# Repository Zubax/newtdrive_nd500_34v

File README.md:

# NewtDrive ND500-34V / Zubax Sadulli

Sadulli is an open-hardware reference design of a 500 W integrated propeller drive based on the
[Mitochondrik LV](http://zubax.com/mitochondrik-lv) motor control chip.
It includes a motor and its control electronics in a single compact unit.

The main design goal is to create a compact yet sophisticated motor controller that can be integrated with relatively
small BLDC and PMSM motors (about 40-45 mm in diameter) in a single unit.
Being equipped with a standard mounting hole pattern,
Sadulli can be used as a drop-in replacement for regular standalone motors in various UAV applications.

## Specifications

- Operating voltage range: 4-8S Li-ion LiCoO<sub>2</sub>, 11-34 V
- Maximum continuous power 500 W
- Maximum continuous phase current amplitude 40 A
- [Cyphal](https://telega.zubax.com/)/CAN (formerly UAVCAN) interface compatible with the DS-015 drone standard
- Solderless integration

Sadulli consists of two main parts: a COTS motor and the ESC.
This repository contains the ESC hardware source files only.
There are two design variants of the Sadulli drive.
All of them share the same ESC design.

Variant  | Motor                 | Propeller diameter [inch] | Propeller pitch [inch] | Mass [g]
-------- | --------------------- | ------------------------- | ---------------------- | --------
Alakdan  | Scorpion MII-4010     | 17                        | 6.2                    | 193
Nudo     | N/A                   | N/A                       | N/A                    | 62

Alakdan | Nudo
--|--
 | 

Sadulli is equipped with a single non-redundant Cyphal/CAN interface.
The input power is supplied through a standard XT30 male connector.
The device can deliver 5V to the Cyphal/CAN power delivery network if the respective configuration option is enabled.

Under the hood, Sadulli is a construction of three PCBs (excluding the Mitochondrik).

The main PCB that determines most of Sadulli's properties is the power stage PCB.
The power stage is composed of three [BUK9K6R2-40E](https://www.digikey.com/products/en?keywords=1727-7274-1-ND)
MOSFET arrays.

Parameter                                               | Value
------------------------------------------------------- | -------------------
Drain to Source Voltage (V<sub>ds</sub>)                | 40 V
Current - Continuous Drain (I<sub>d</sub>) @ 25°C       | 40 A
R<sub>ds on</sub> (Max) @ I<sub>d</sub>, V<sub>gs</sub> | 6 mOhm @ 25 A, 10 V
Gate Charge (Q<sub>g</sub>) (Max) @ V<sub>gs</sub>      | 35.4 nC @ 10 V

The resistance of the phase current shunts is 3 mOhm.

The bulk capacitor bank is formed with 6
[68µF aluminum electrolytic capacitors](https://www.digikey.com/product-detail/en/w-rth-elektronik/860020673014/732-8860-3-ND/5727097).

### Telega configuration

The Mitochondrik LV module installed in Sadulli needs to be configured such that it is aware of the parameters of the power stage
(and the motor).
To achieve this, upload the following configuration:

```yaml
# Refer to the Mitochondrik-LV datasheet for the explanation of how the parameter values have been found.
vsi.bridge_resistance:    [0.003, 0.006, 0.003, 0.006, 0.003, 0.003]                            # [ohm]
vsi.phase_current_gain:   [33.333333333333, 33.333333333333, 8.333333333333, 8.333333333333]    # [ampere/volt]
vsi.phase_current_stderr: [0.2, 0.2, 0.1, 0.1]                                                  # [ampere]
vsi.thermistor_v2k:       [223.15, 100.0, 0.0]                                                  # for MCP9700

motor.current_ctl_bwr:  0.04
motor.current_max:      38.0
motor.mechanical_ratio: 7                   # The motor has 14 poles.
motor.inductance_dq:    [29.0e-6, 29.0e-6]
motor.resistance:       0.0508
motor.flux_linkage:     0.002115
motor.current_ramp:     5000.0
motor.voltage_ramp:     20.0
# The thermistor coefficients are valid for:
# R_pull = 1.2 kohms; R_io = 0; V_pull = 3.3 V
# Thermistor models: KTY81/120, KTY81/110, KTY81/121, KTY81/122, KTY81/150, 102PS1J, 102PS1G.
motor.thermistor_v2k: [151.24172662, 36.46076996, 40.65372514]

aux.pull: +1                    # Pull up the thermistor input.

sys.debug: false                # Turn off the in-circuit debug interfaces to enhance EMI immunity.
sys.golden: sys. vsi. motor. aux.pull # Retain these parameter groups across a factory reset.
```

Refer to the Telega Reference Manual for details.

## Release notes

### Sadulli v1.5 (May 2023)

* Added Alakdan variant using Scorpion MII-4010 motor.
* Removed Grosso and Piccino variants using SunnySky motors.
* Updated assembly guide.
* Increased the hardware over-current protection limit (R1 on the connectors PCB increased to 27k).
* Added thermistor alternatives:

Original  | Alternatives
--------- | -----------------
KTY81/120 | KTY81/110, KTY81/121, KTY81/122, KTY81/150, 102PS1J, 102PS1G

### Sadulli v1.0 (January 2021)

First stable release. There have been no substantial changes compared to the pre-production revision.

## License

This project is licensed under the terms of [CC-BY 4.0](https://creativecommons.org/licenses/by/4.0/).

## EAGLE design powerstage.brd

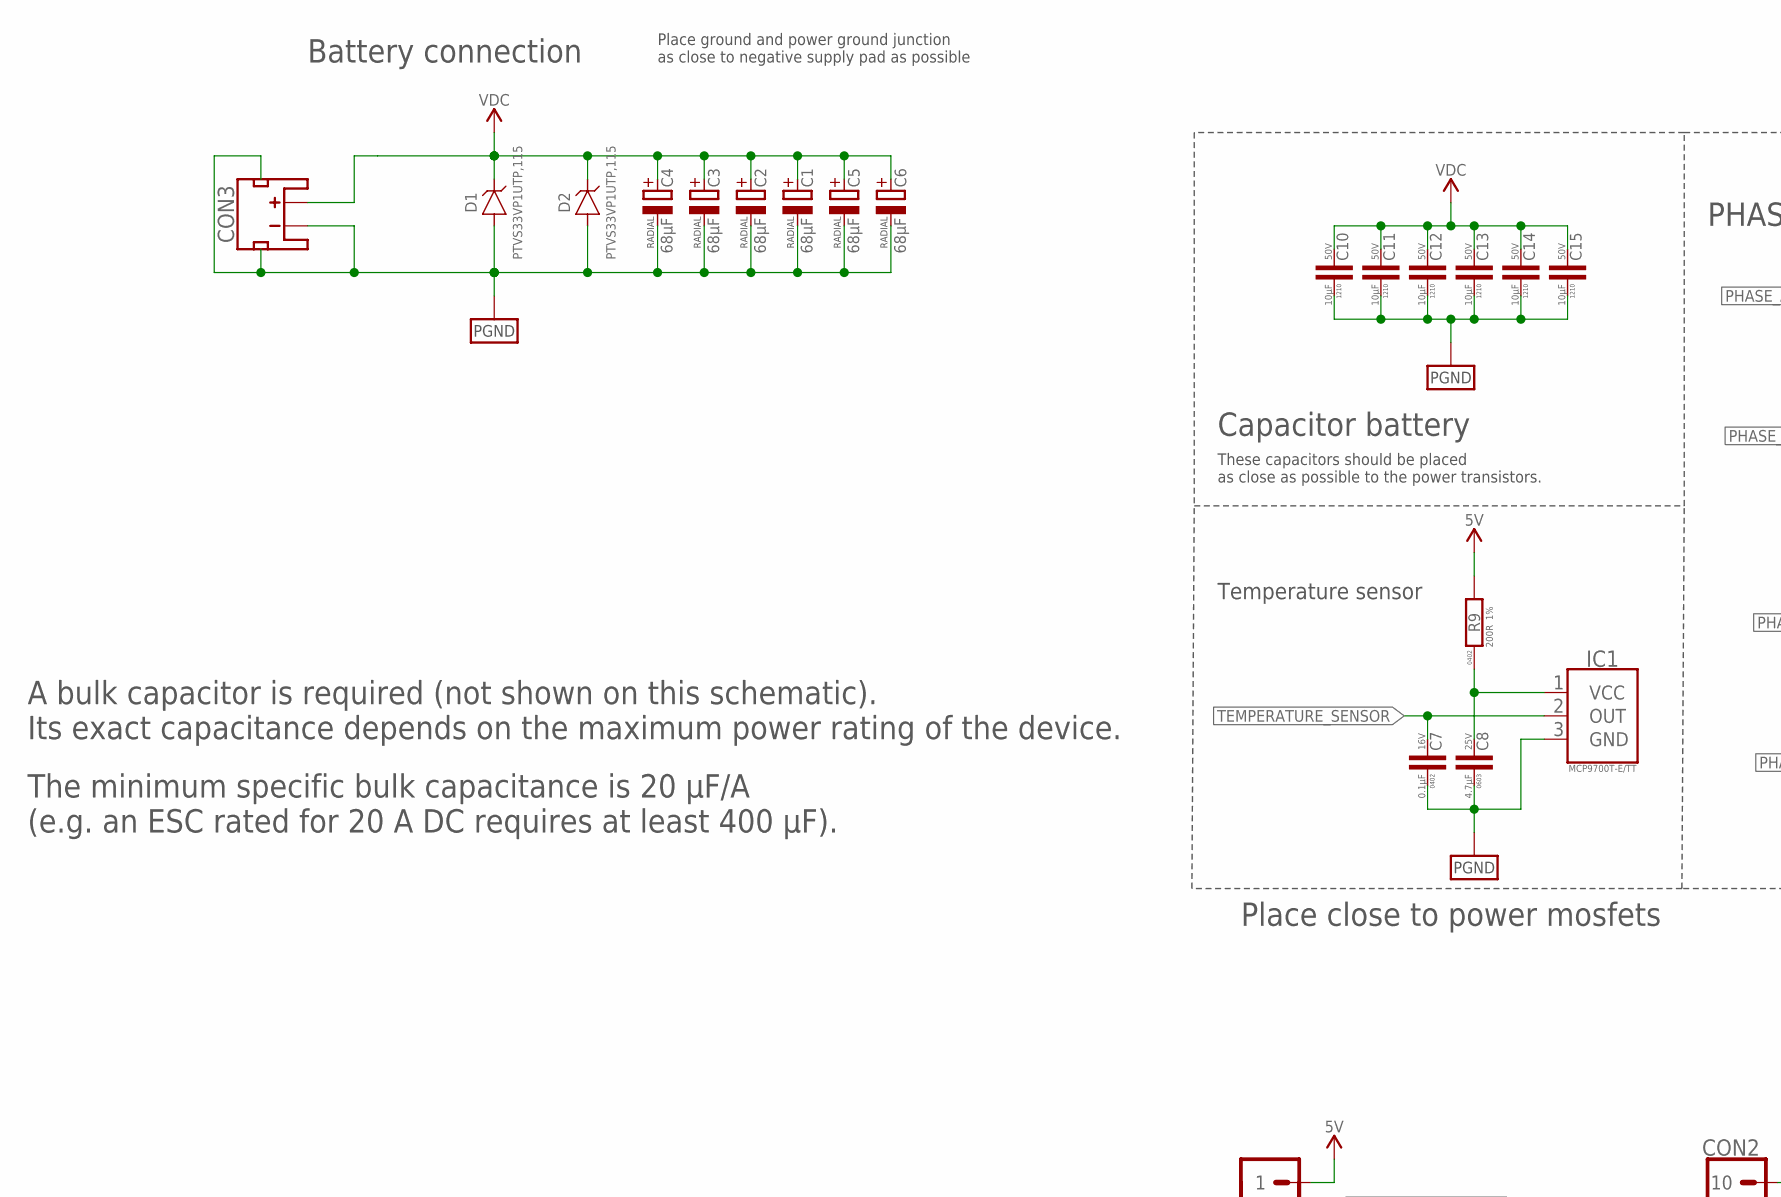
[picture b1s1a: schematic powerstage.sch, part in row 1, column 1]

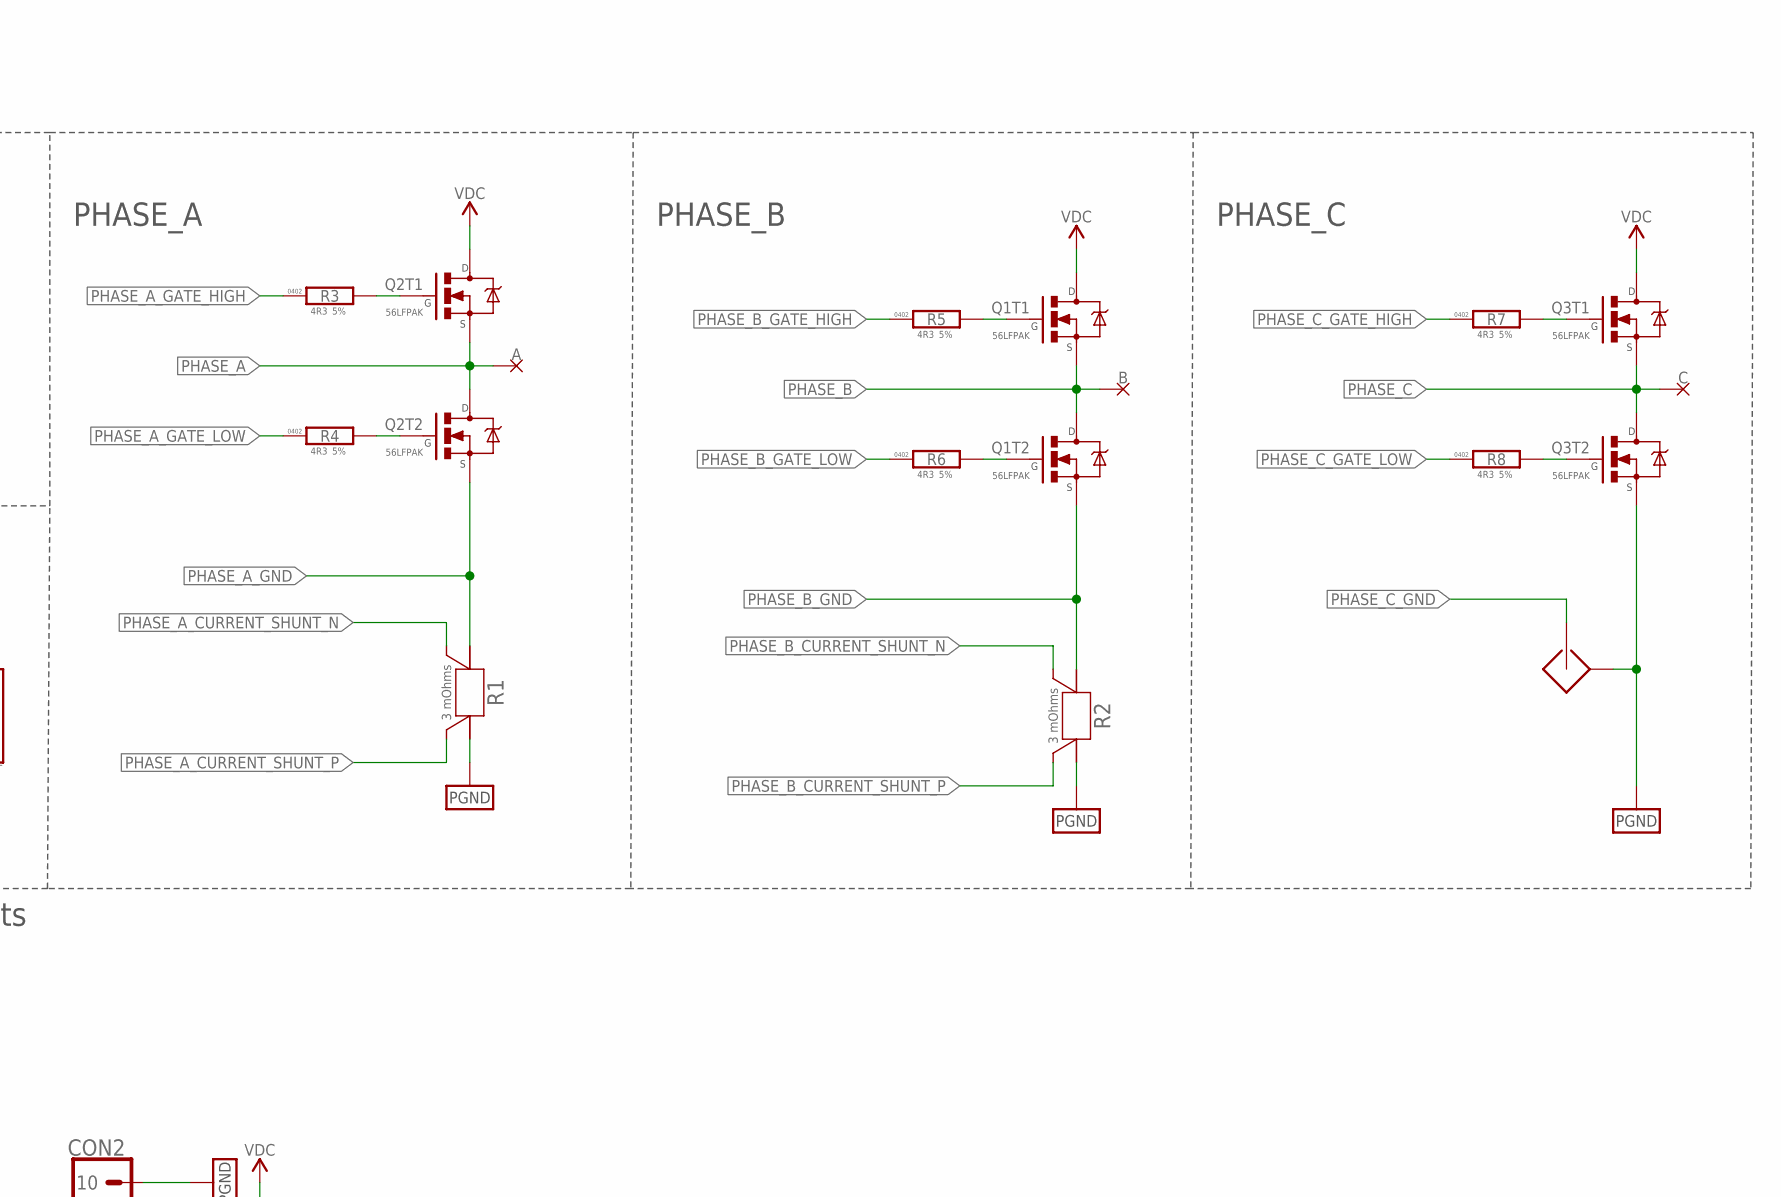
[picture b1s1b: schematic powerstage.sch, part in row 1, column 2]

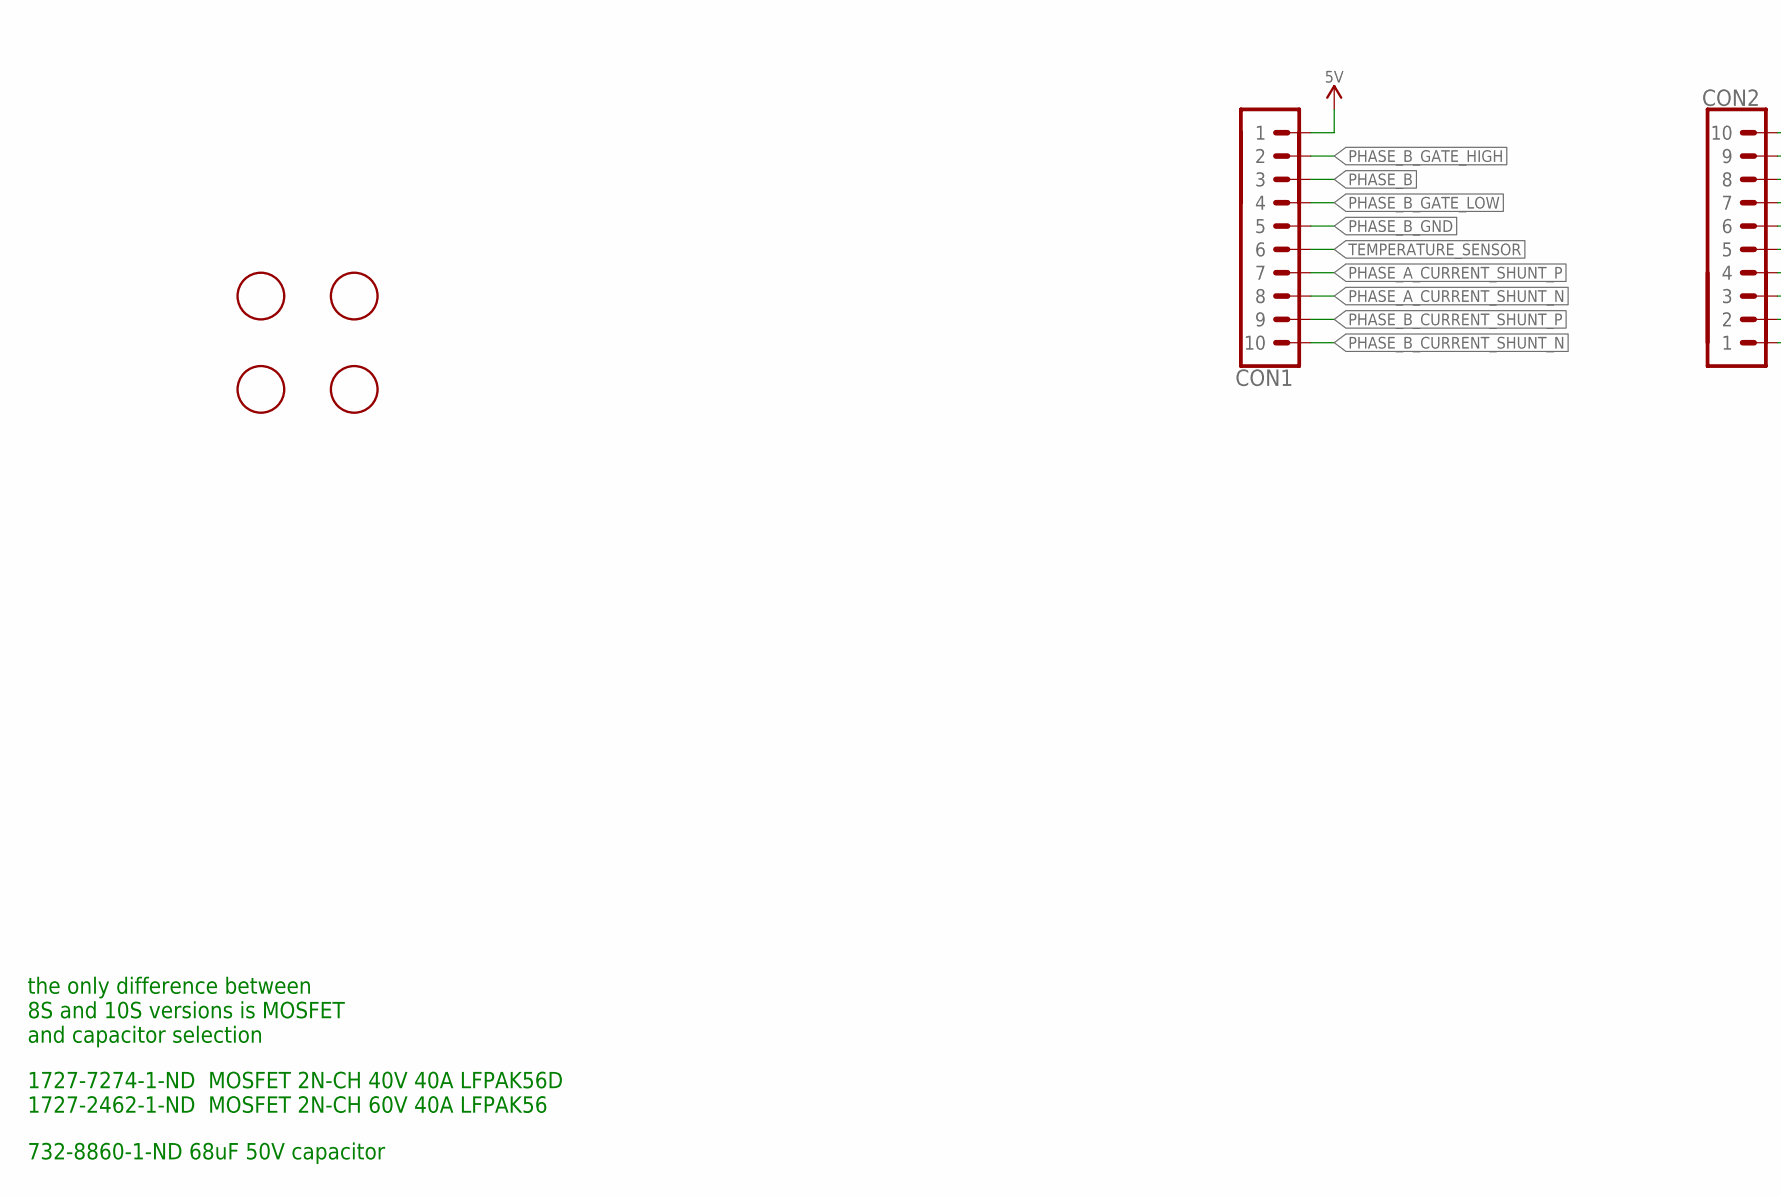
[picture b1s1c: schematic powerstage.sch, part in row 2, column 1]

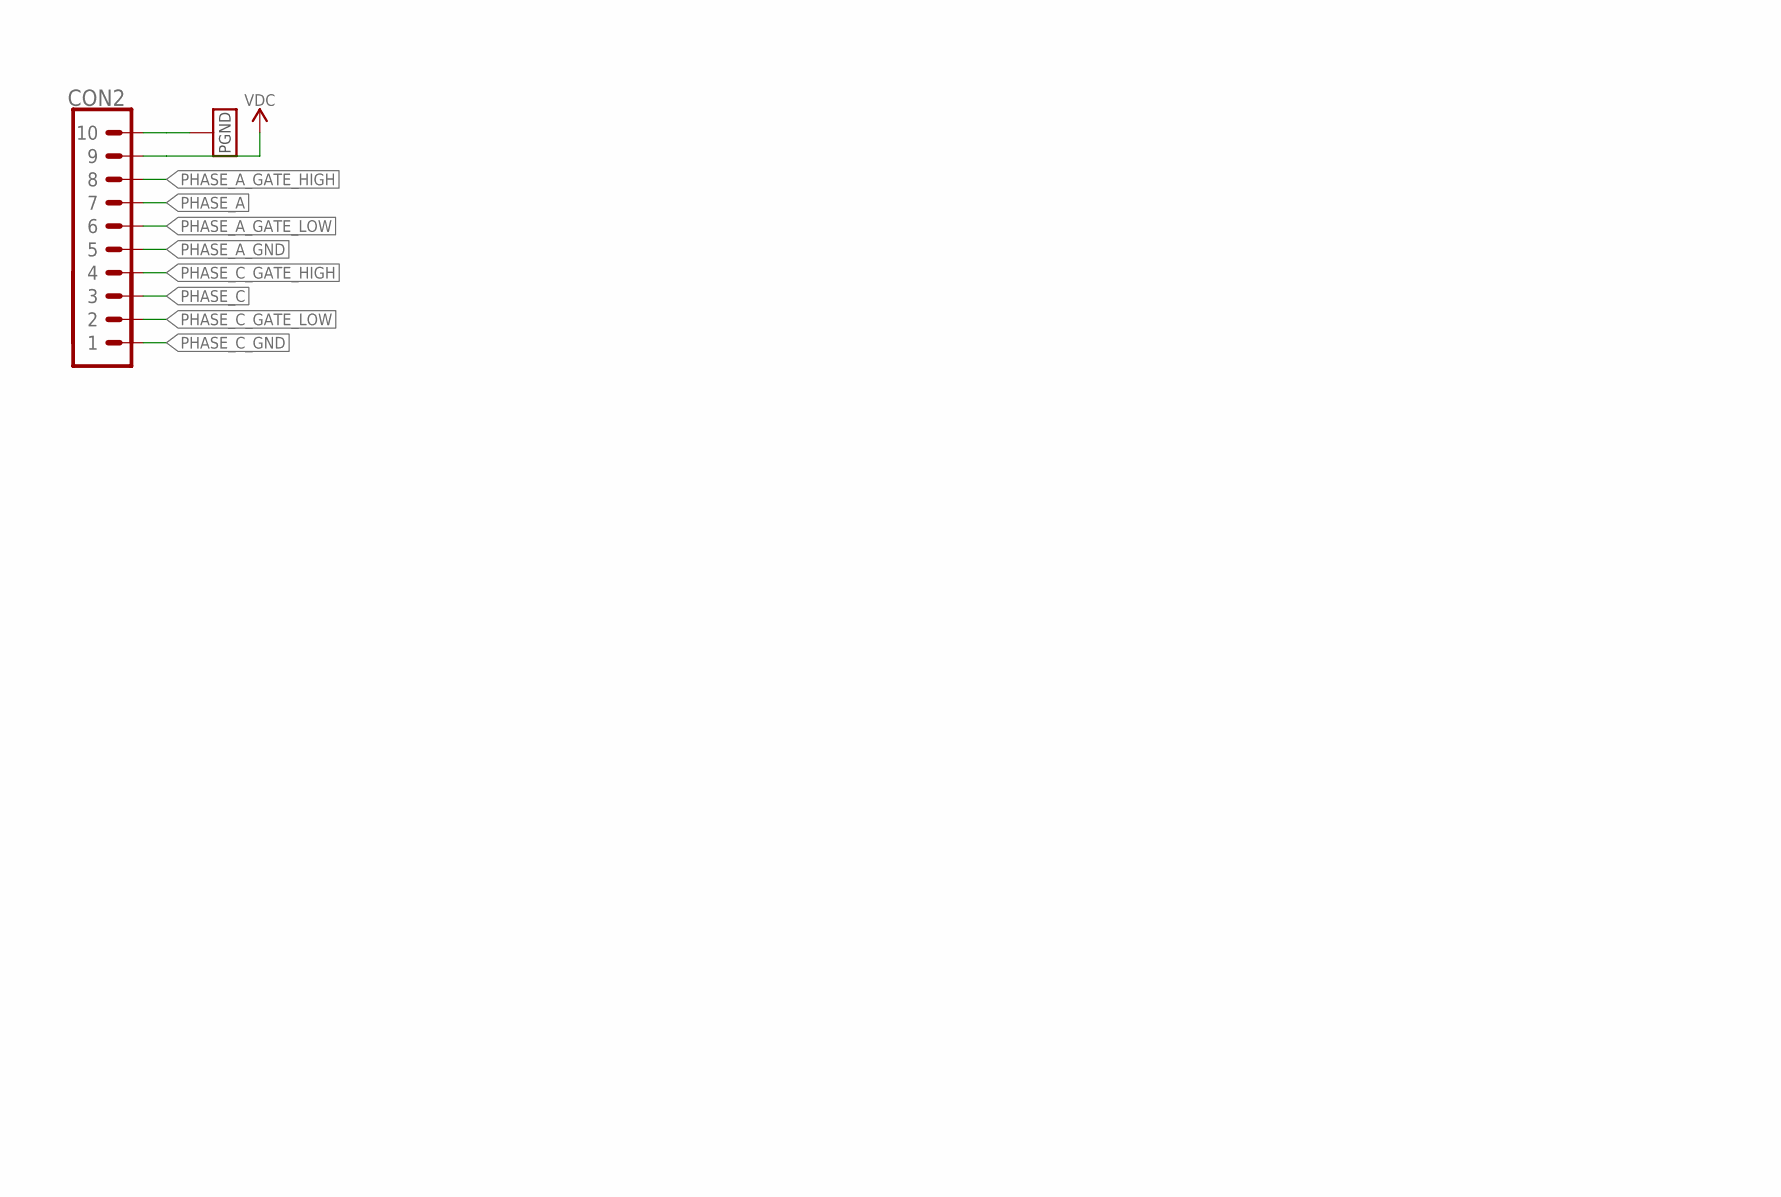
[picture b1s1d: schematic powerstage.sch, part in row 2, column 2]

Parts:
A: PAD-HOLE_2; HOLE_2
B: PAD-HOLE_2; HOLE_2
C: PAD-HOLE_2; HOLE_2
C1, C2, C3, C4: 68µF; RADIAL_6.3X12.5-RA
C5, C6: 68µF; RADIAL_6.3X12.5; DIGIKEY# 732-8860-1-ND
C7: 0.1µF; C0402
C8: 4.7µF; C0603
C10, C11, C12, C13, C14, C15: 10µF; C1210
CON1, CON2: PINHEAD_1X10-2-FEMALE; 1X10-PTH_2-FEMALE
CON3: BATTERY_CON-2P-XT30-RA; XT30-RA
D1, D2: PTVS33VP1UTP,115-36V-SOD128; SOD128
IC1: MCP9700; SOT23B-3
Q1, Q2, Q3: BUK9K6R2-40E,115; SOT-1205
R1, R2: 3 mOhms; R2512-KELVIN
R3, R4, R5, R6, R7, R8: 4R3; R0402
R9: 200R; R0402
S1: SENSE; SENSE-0.6
U$8, U$9, U$10, U$12: FIDUCIALMOUNT; FIDUCIA-MOUNT

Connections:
unnamed: Q2.2 (G), R3.2
unnamed: Q2.4 (G), R4.2
unnamed: Q1.2 (G), R5.2
unnamed: Q1.4 (G), R6.2
unnamed: C8.P$2 (2), IC1.1 (VCC), R9.1
unnamed: Q3.2 (G), R7.2
unnamed: Q3.4 (G), R8.2
PGND: C1.-, C2.-, C3.-, C4.-, C5.-, C6.-, C7.1, C8.P$1 (1), C10.1, C11.1, C12.1, C13.1, C14.1, C15.1, CON2.10, CON3.-, CON3.P$3 (PAD1), CON3.P$4 (PAD2), D1.A, D2.A, IC1.3 (GND), Q3.3 (S), R1.2, R1.22 (2), R2.2, R2.22 (2), S1.SHELL (SHELLL)
PHASE_A: A.P$1, CON2.7, Q2.1 (S), Q2.5 (D), Q2.6 (D), Q2.EP-5-6 (D)
PHASE_A_CURRENT_SHUNT_N: CON1.8, R1.S1
PHASE_A_CURRENT_SHUNT_P: CON1.7, R1.S2
PHASE_A_GATE_HIGH: CON2.8, R3.1
PHASE_A_GATE_LOW: CON2.6, R4.1
PHASE_A_GND: CON2.5, Q2.3 (S), R1.1, R1.11 (1)
PHASE_B: B.P$1, CON1.3, Q1.1 (S), Q1.5 (D), Q1.6 (D), Q1.EP-5-6 (D)
PHASE_B_CURRENT_SHUNT_N: CON1.10, R2.S1
PHASE_B_CURRENT_SHUNT_P: CON1.9, R2.S2
PHASE_B_GATE_HIGH: CON1.2, R5.1
PHASE_B_GATE_LOW: CON1.4, R6.1
PHASE_B_GND: CON1.5, Q1.3 (S), R2.1, R2.11 (1)
PHASE_C: C.P$1, CON2.3, Q3.1 (S), Q3.5 (D), Q3.6 (D), Q3.EP-5-6 (D)
PHASE_C_GATE_HIGH: CON2.4, R7.1
PHASE_C_GATE_LOW: CON2.2, R8.1
PHASE_C_GND: CON2.1, S1.IN
TEMPERATURE_SENSOR: C7.2, CON1.6, IC1.2 (OUT)
VDC: C1.+, C2.+, C3.+, C4.+, C5.+, C6.+, C10.2, C11.2, C12.2, C13.2, C14.2, C15.2, CON2.9, CON3.+, D1.C, D2.C, Q1.7 (D), Q1.8 (D), Q1.EP-7-8 (D), Q2.7 (D), Q2.8 (D), Q2.EP-7-8 (D), Q3.7 (D), Q3.8 (D), Q3.EP-7-8 (D)
VDD_5V: CON1.1, R9.2

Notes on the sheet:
PHASE_A
PHASE_B
PHASE_C
A bulk capacitor is required (not shown on this schematic). Its exact capacitance depends on the maximum power rating of the device.
Capacitor battery
These capacitors should be placed as close as possible to the power transistors.
Temperature sensor
Battery connection
The minimum specific bulk capacitance is 20 μF/A (e.g. an ESC rated for 20 A DC requires at least 400 μF).
Place ground and power ground junction as close to negative supply pad as possible
Place close to power mosfets
1727-7274-1-ND MOSFET 2N-CH 40V 40A LFPAK56D 1727-2462-1-ND MOSFET 2N-CH 60V 40A LFPAK56
the only difference between 8S and 10S versions is MOSFET and capacitor selection
732-8860-1-ND 68uF 50V capacitor

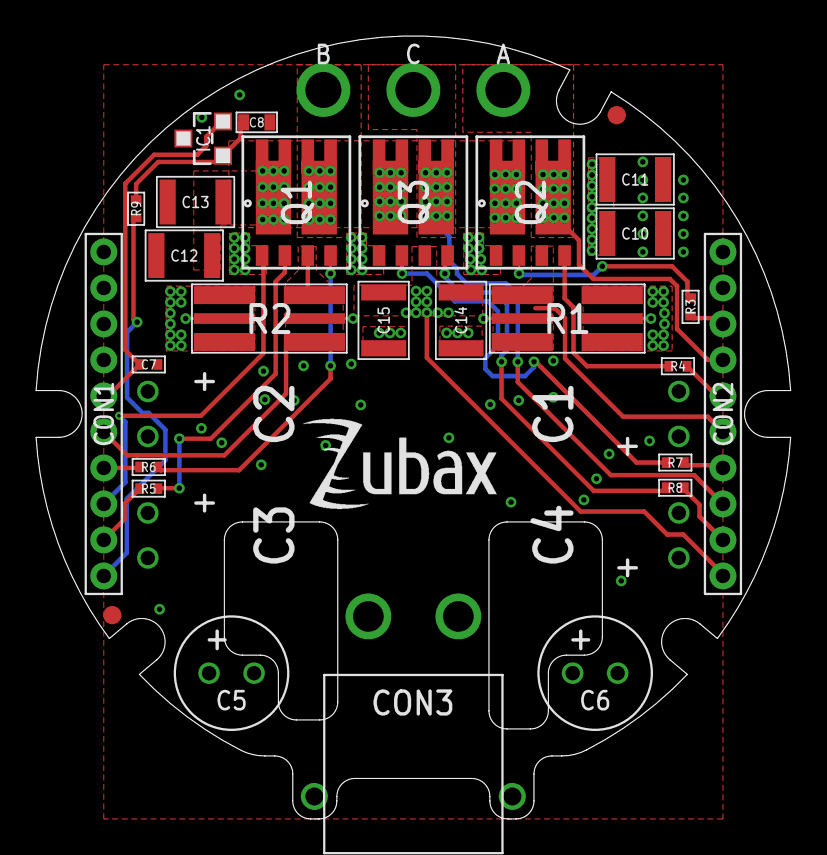
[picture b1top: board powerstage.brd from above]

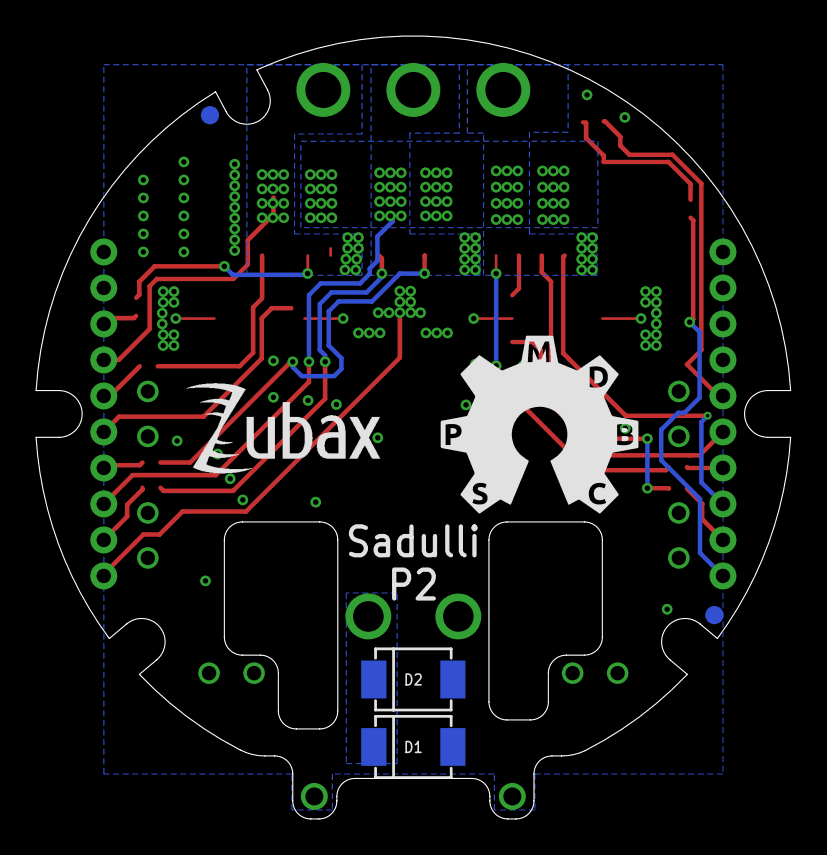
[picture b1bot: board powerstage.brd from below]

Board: 4 copper layers, 41.9 x 43.5 mm, 44 parts (6 on the bottom side), 27 nets.

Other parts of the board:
U$1, U$13: ZUBAX_LOGO_5X10
U$2: DUCK_6X5
U$4: OSHW-10.5X11.5

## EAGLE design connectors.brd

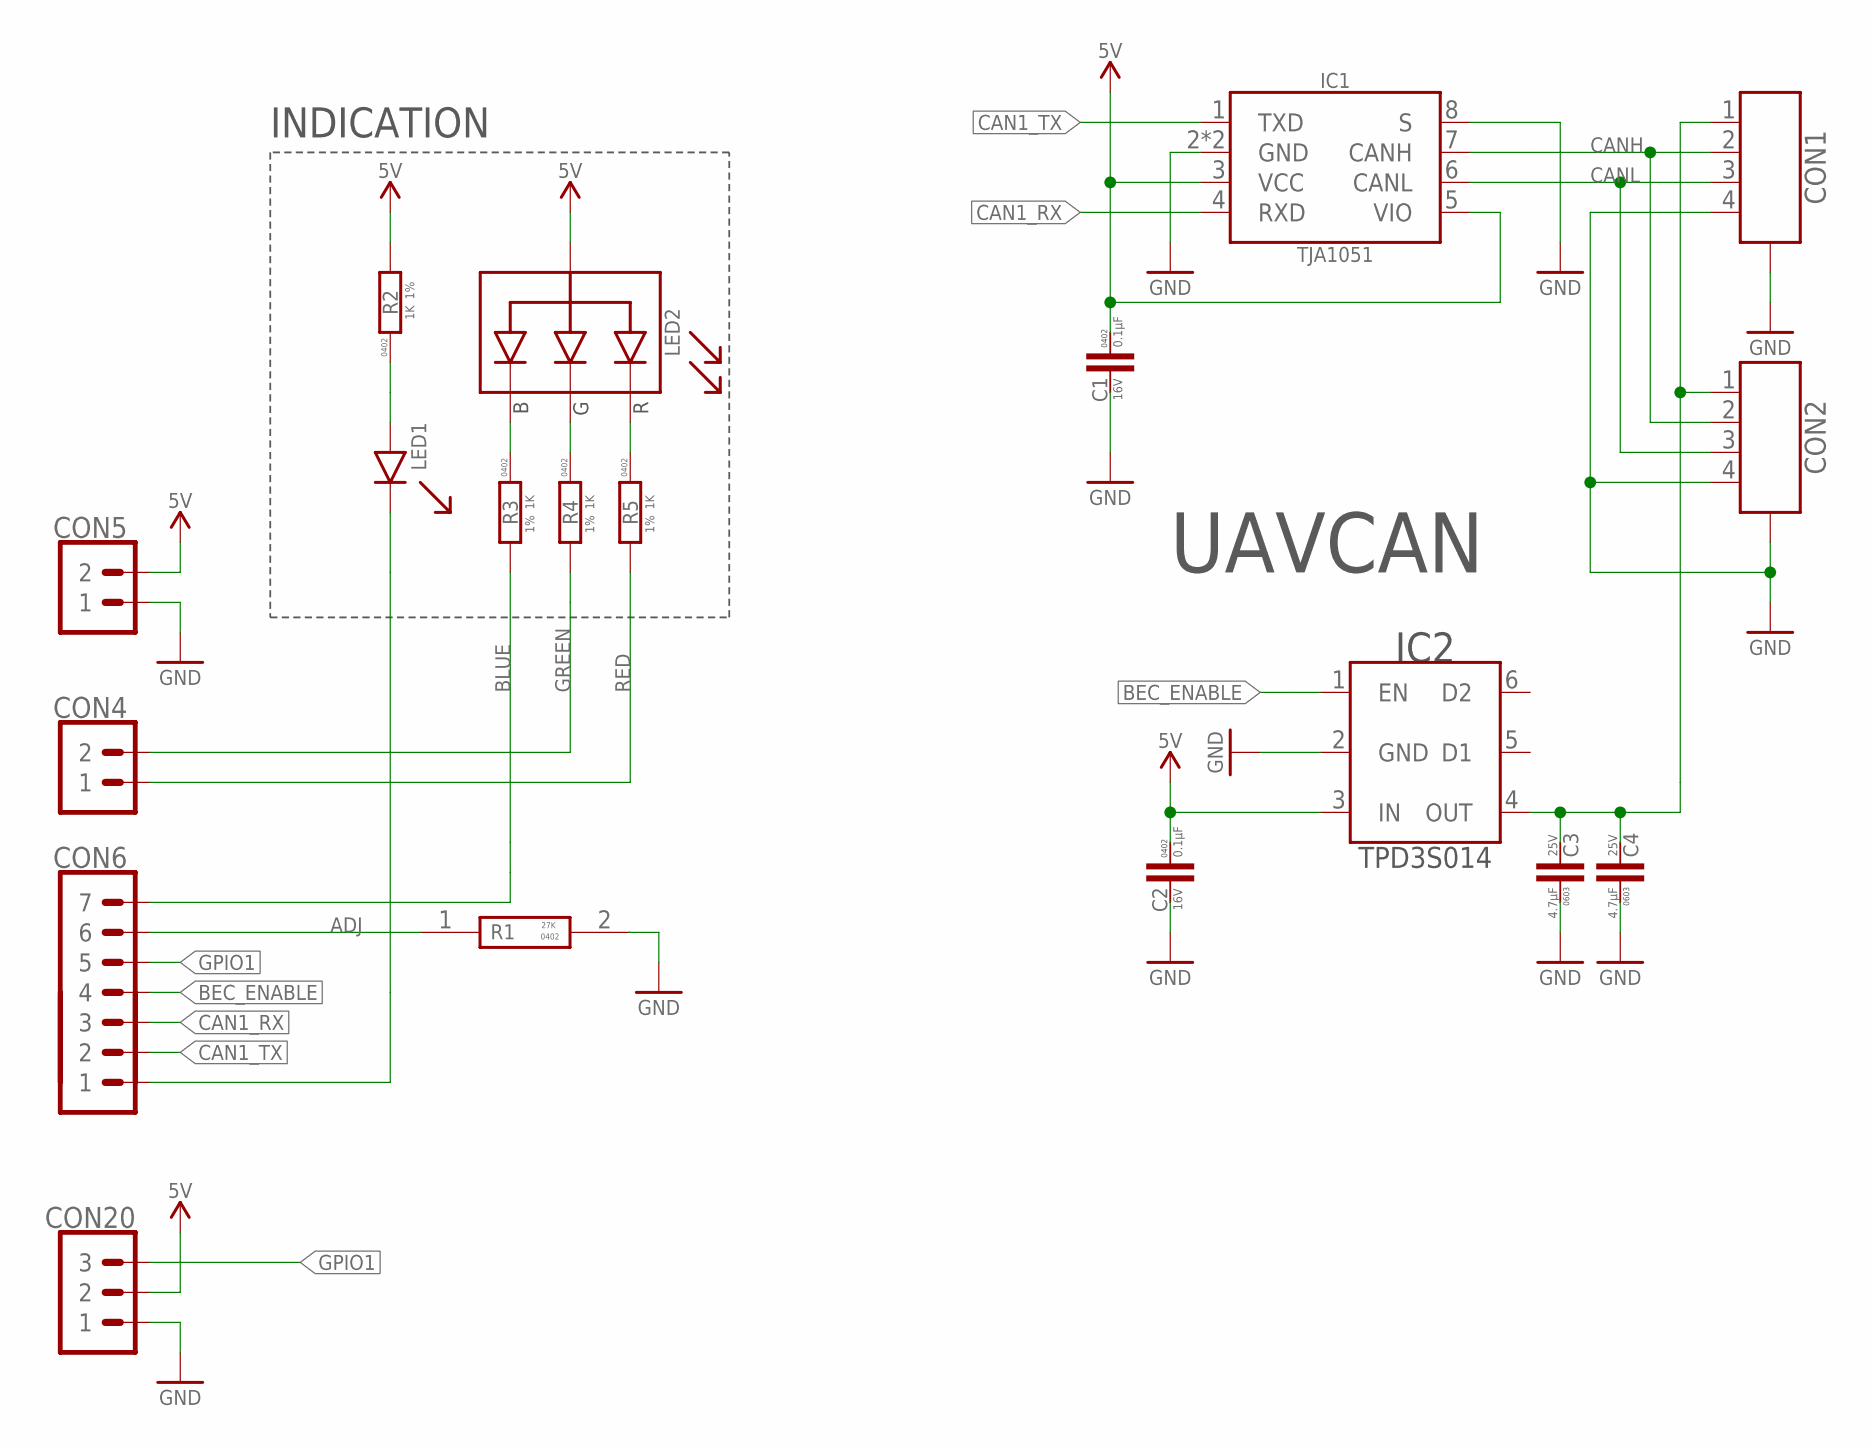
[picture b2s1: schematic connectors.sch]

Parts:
C1, C2: 0.1µF; C0402
C3, C4: 4.7µF; C0603
CON1, CON2: CON-4P-TABS-JST_GH-RA; JST_GH-4P-RA
CON4, CON5: PINHEAD_1X02-2; 1X02-PTH-2
CON6: PINHEAD_1X07-2; 1X07-PTH-2
CON20: PINHEAD_1X03-2.54-RA; 1X03-PTH-2.54-RA
IC1: TJA1051; SOT782-1
IC2: TPD3S014DBVR-SOT23-6; SOT26
LED1: GREEN; 0402_LED
LED2: LTST-C19HE1WT; LITE_ON_RGB_LED
R1: 27K; RESC1005X40N; MANUFACTURER_PART_NUMBER AF0402FR-0727KL
R2, R3, R4, R5: 1K; R0402

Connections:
ADJ: CON6.6, R1.1
BEC_ENABLE: CON6.4, IC2.1 (EN)
BLUE: CON6.7, R3.2
CAN1_LED: CON6.1, LED1.C
CAN1_RX: CON6.3, IC1.4 (RXD)
CAN1_TX: CON6.2, IC1.1 (TXD)
CAN1_VDD: C3.P$2 (2), C4.P$2 (2), CON1.1, CON2.1, IC2.4 (OUT)
CANH: CON1.2, CON2.2, IC1.7 (CANH)
CANL: CON1.3, CON2.3, IC1.6 (CANL)
GND: C1.2, C2.2, C3.P$1 (1), C4.P$1 (1), CON1.4, CON1.M$0 (GND), CON1.M$1 (GND), CON2.4, CON2.M$0 (GND), CON2.M$1 (GND), CON5.1, CON20.1, IC1.2 (GND), IC1.8 (S), IC1.PAD (GND), IC2.2 (GND), R1.2
GPIO1: CON6.5, CON20.3
GREEN: CON4.2, R4.2
unnamed: LED1.A, R2.1
unnamed: LED2.R, R5.1
unnamed: LED2.G, R4.1
unnamed: LED2.B, R3.1
RED: CON4.1, R5.2
VDD_5V: C1.1, C2.1, CON5.2, CON20.2, IC1.3 (VCC), IC1.5 (VIO), IC2.3 (IN), LED2.+ (A), R2.2

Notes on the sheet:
INDICATION
UAVCAN

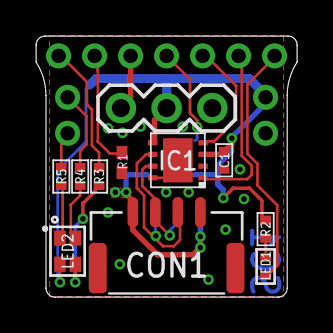
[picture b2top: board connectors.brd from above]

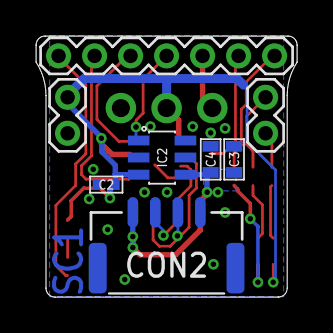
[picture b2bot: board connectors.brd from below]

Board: 2 copper layers, 14.5 x 14.5 mm, 19 parts (8 on the bottom side), 18 nets.

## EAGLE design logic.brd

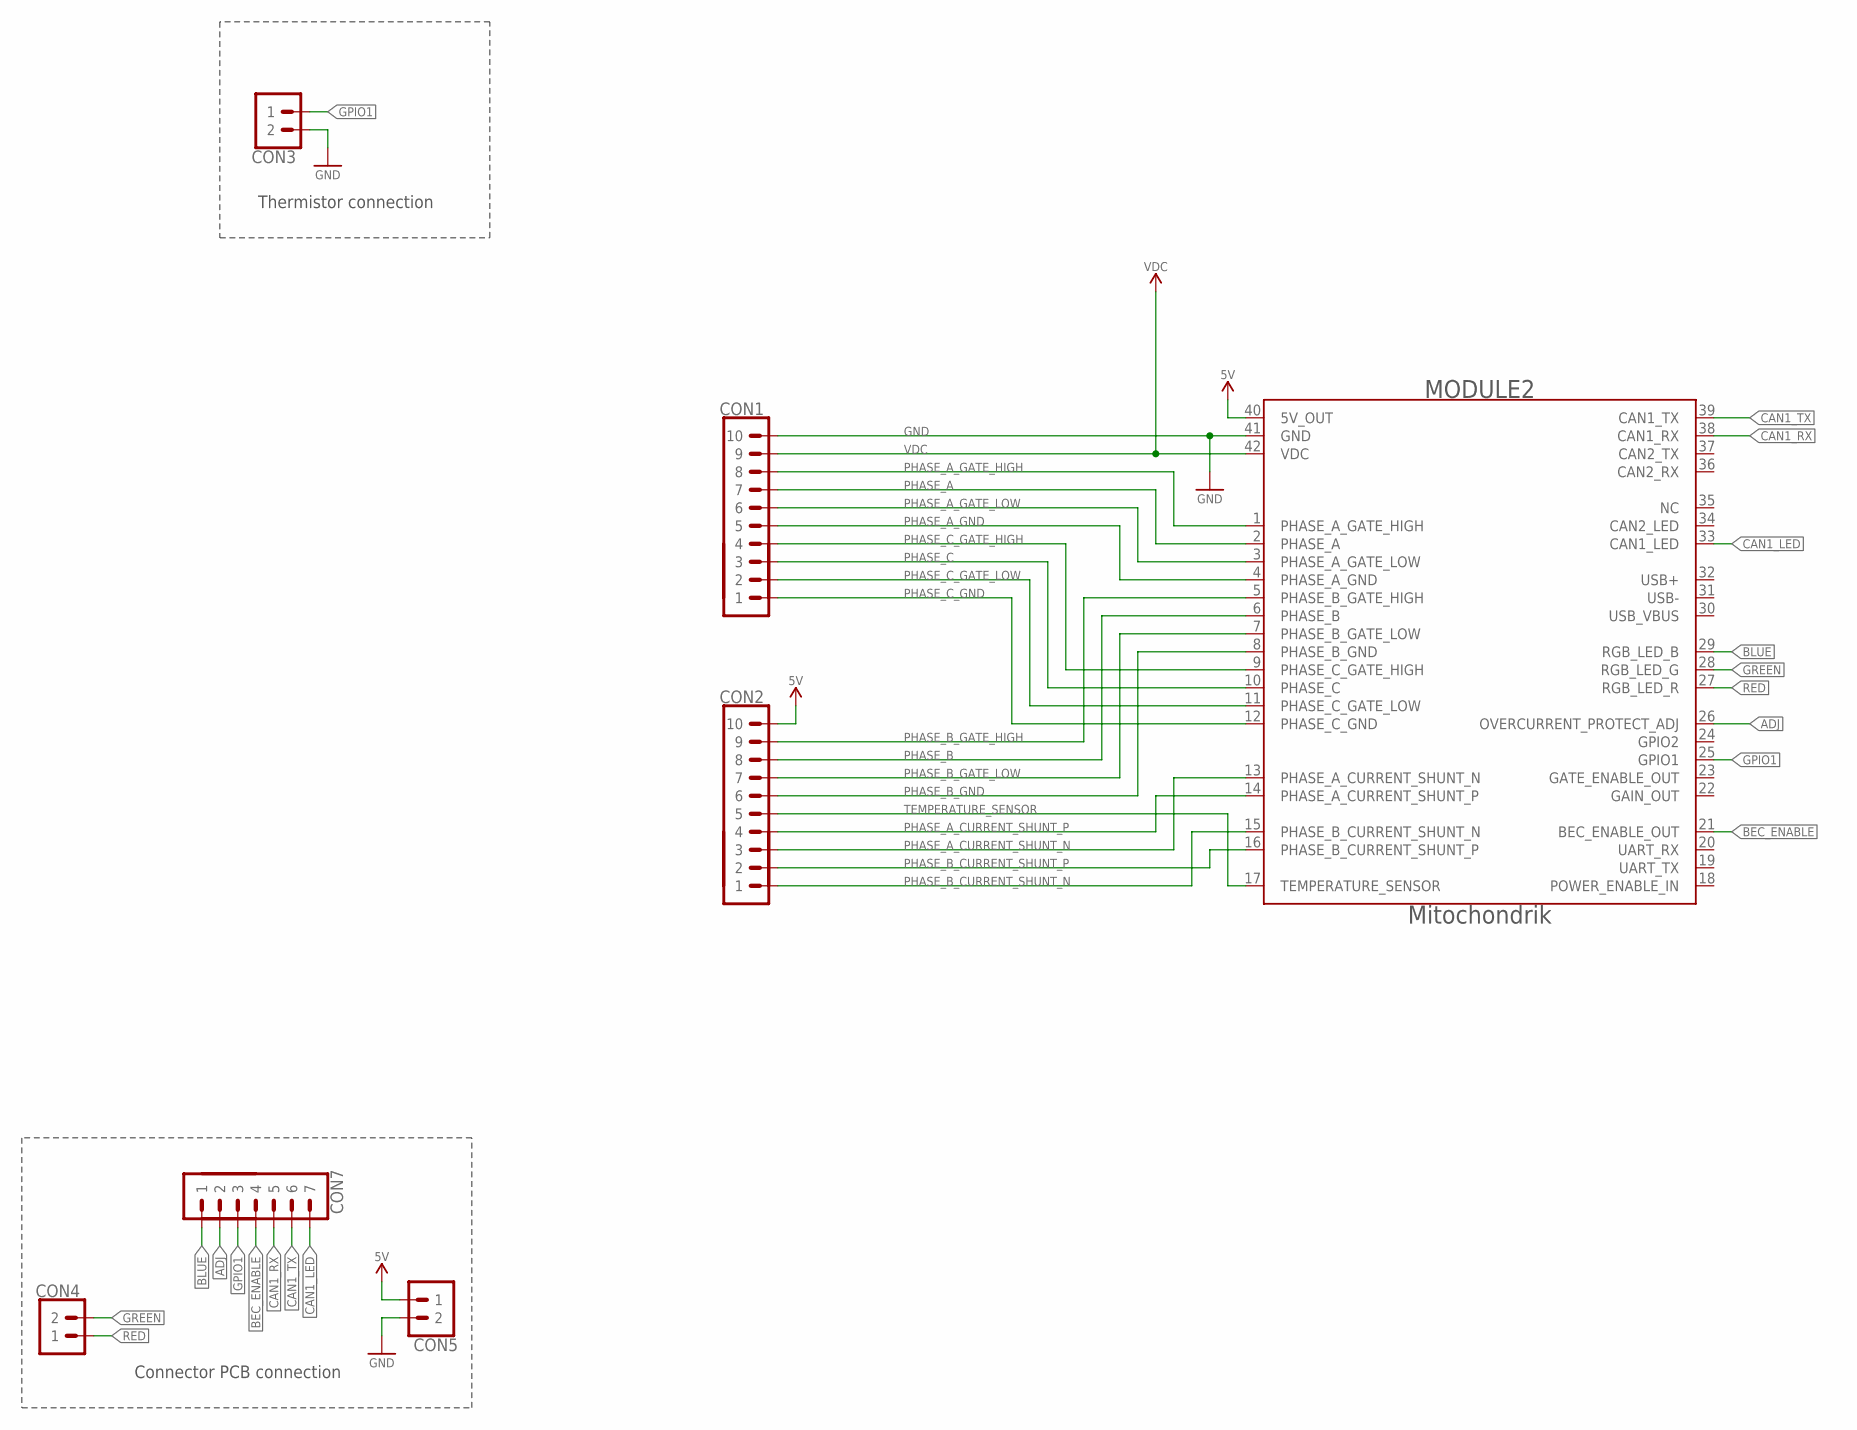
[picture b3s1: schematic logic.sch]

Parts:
CON1, CON2: PINHEAD_1X10-2; 1X10-PTH_2
CON3, CON4, CON5: PINHEAD_1X02-2; 1X02-PTH-2
CON7: PINHEAD_1X07-2; 1X07-PTH-2
MODULE2: MITOHONDRIQUE_V0.2-TH; MITOHONDRIQUE-TH

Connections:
ADJ: CON7.2, MODULE2.26 (OVERCURRENT_PROTECT_ADJ)
BEC_ENABLE: CON7.4, MODULE2.21 (BEC_ENABLE_OUT)
BLUE: CON7.1, MODULE2.29 (RGB_LED_B)
CAN1_LED: CON7.7, MODULE2.33 (CAN1_LED)
CAN1_RX: CON7.5, MODULE2.38 (CAN1_RX)
CAN1_TX: CON7.6, MODULE2.39 (CAN1_TX)
GND: CON1.10, CON3.2, CON5.2, MODULE2.41 (GND)
GPIO1: CON3.1, CON7.3, MODULE2.25 (GPIO1)
GREEN: CON4.2, MODULE2.28 (RGB_LED_G)
PHASE_A: CON1.7, MODULE2.2 (PHASE_A)
PHASE_A_CURRENT_SHUNT_N: CON2.3, MODULE2.13 (PHASE_A_CURRENT_SHUNT_N)
PHASE_A_CURRENT_SHUNT_P: CON2.4, MODULE2.14 (PHASE_A_CURRENT_SHUNT_P)
PHASE_A_GATE_HIGH: CON1.8, MODULE2.1 (PHASE_A_GATE_HIGH)
PHASE_A_GATE_LOW: CON1.6, MODULE2.3 (PHASE_A_GATE_LOW)
PHASE_A_GND: CON1.5, MODULE2.4 (PHASE_A_GND)
PHASE_B: CON2.8, MODULE2.6 (PHASE_B)
PHASE_B_CURRENT_SHUNT_N: CON2.1, MODULE2.15 (PHASE_B_CURRENT_SHUNT_N)
PHASE_B_CURRENT_SHUNT_P: CON2.2, MODULE2.16 (PHASE_B_CURRENT_SHUNT_P)
PHASE_B_GATE_HIGH: CON2.9, MODULE2.5 (PHASE_B_GATE_HIGH)
PHASE_B_GATE_LOW: CON2.7, MODULE2.7 (PHASE_B_GATE_LOW)
PHASE_B_GND: CON2.6, MODULE2.8 (PHASE_B_GND)
PHASE_C: CON1.3, MODULE2.10 (PHASE_C)
PHASE_C_GATE_HIGH: CON1.4, MODULE2.9 (PHASE_C_GATE_HIGH)
PHASE_C_GATE_LOW: CON1.2, MODULE2.11 (PHASE_C_GATE_LOW)
PHASE_C_GND: CON1.1, MODULE2.12 (PHASE_C_GND)
RED: CON4.1, MODULE2.27 (RGB_LED_R)
TEMPERATURE_SENSOR: CON2.5, MODULE2.17 (TEMPERATURE_SENSOR)
VDC: CON1.9, MODULE2.42 (VDC)
VDD_5V: CON2.10, CON5.1, MODULE2.40 (5V_OUT)

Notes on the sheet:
Thermistor connection
Connector PCB connection

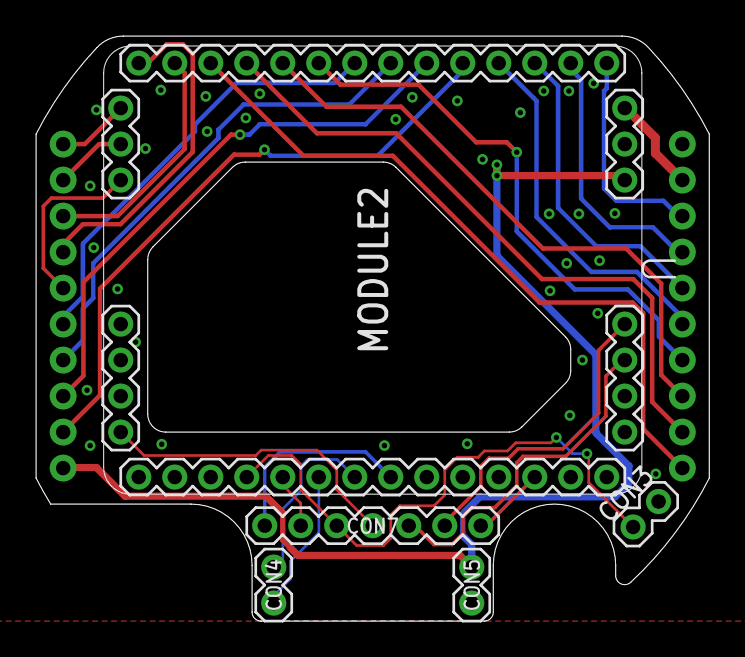
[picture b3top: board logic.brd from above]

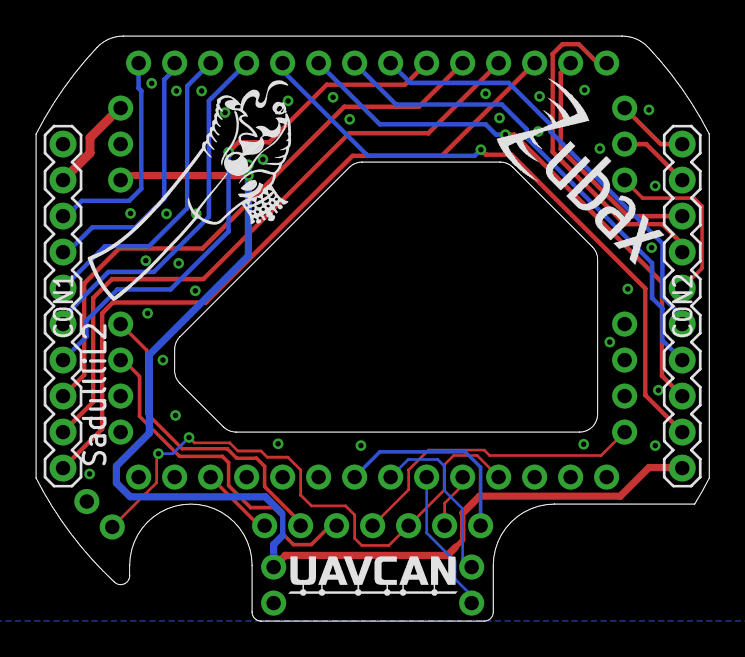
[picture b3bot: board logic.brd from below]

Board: 2 copper layers, 37.4 x 32.5 mm, 10 parts (5 on the bottom side), 29 nets.

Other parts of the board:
U$1: ZUBAX_LOGO_5X10
U$3: UAVCAN_9X2.5
U$5: DRAGON-15X6

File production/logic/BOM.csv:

"Qty";"Value";"Device";"Package";"Parts";"Description";"MANF";"MANF#";
"1";"MITOHONDRIQUE-TH";"MITOHONDRIQUE-TH";"MITOHONDRIQUE";"MODULE1";"";"Zubax Robotics";"Mitochondrik";
"2";"PINHEAD_1X02-2";"PINHEAD_1X02-2";"1X02-PTH-2";"CON4, CON5";"pinheader 2P";"";"";
"1";"PINHEAD_1X07-2";"PINHEAD_1X07-2";"1X07-PTH-2";"CON7";"pinheader 7P";"";"";
"2";"PINHEAD_1X10-2";"PINHEAD_1X10-2";"1X10-PTH_2";"CON1, CON2";"";"";"";
